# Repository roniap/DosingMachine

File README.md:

# DosingMachine
Automatic dosing sistem for  fertilization

1. PCB EC & PH
2. PROBE STL 3D
3. NEXT TO DO. . . .

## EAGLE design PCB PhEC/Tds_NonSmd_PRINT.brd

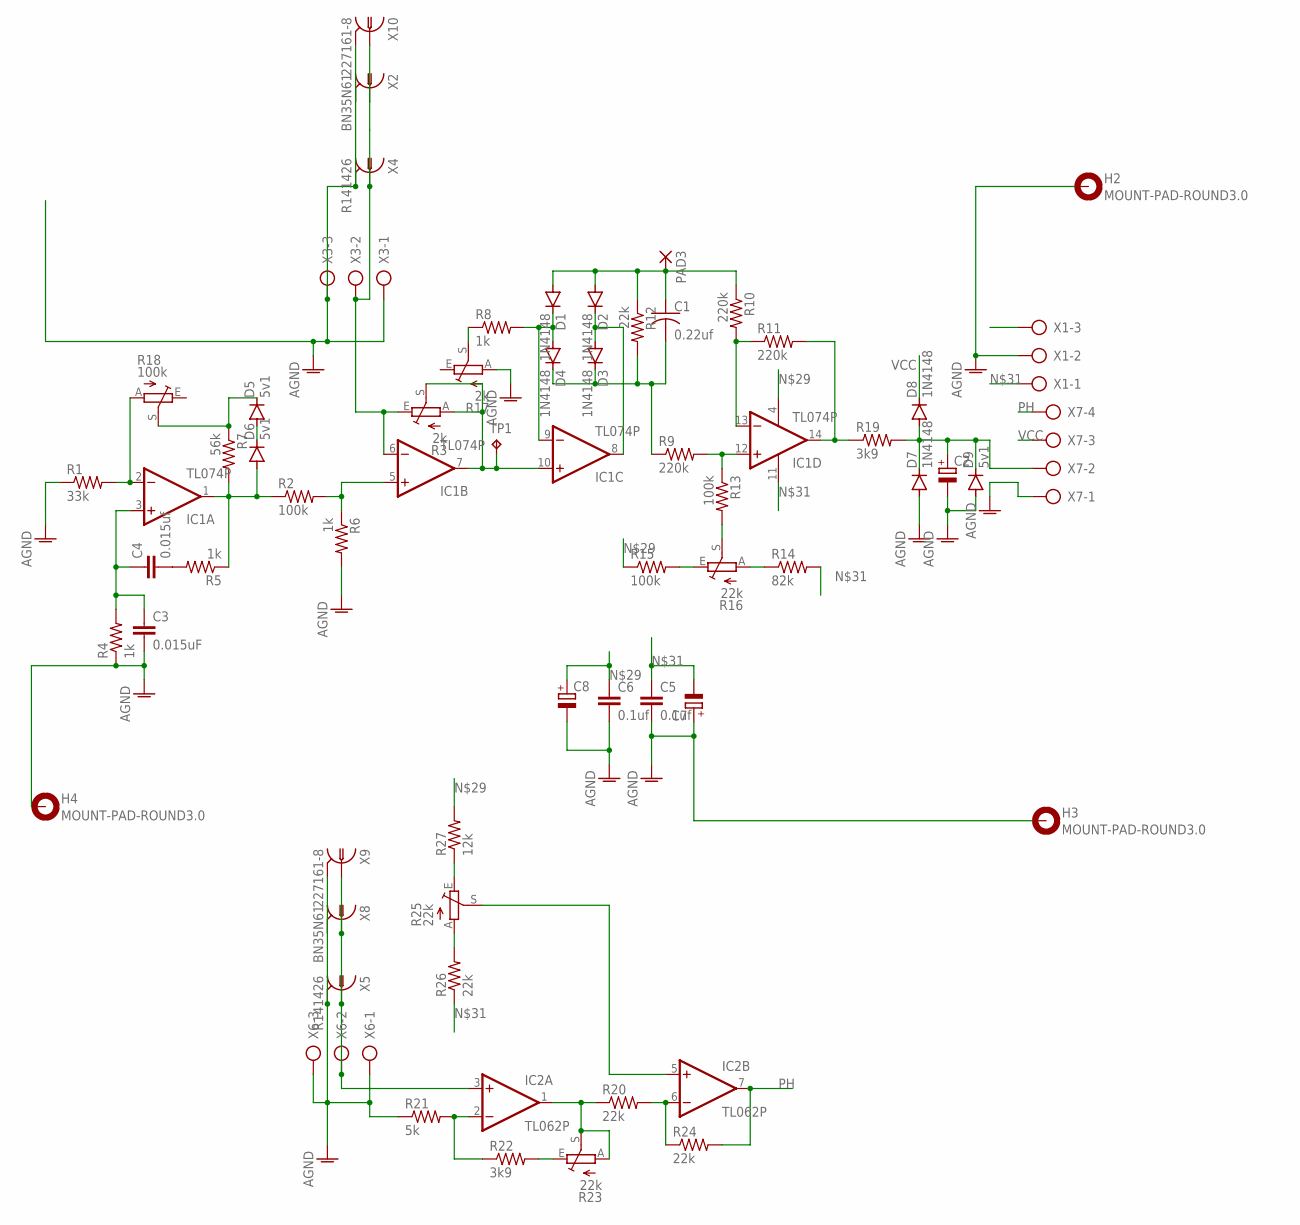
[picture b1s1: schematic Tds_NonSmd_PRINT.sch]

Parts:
C1: 0.22uf; C050-024X044
C2, C7, C8: CPOL-EUE5-8.5; E5-8,5
C3: 0.015uF; C050-024X044
C4: 0.015uf; C050-024X044
C5, C6: 0.1uf; C5B2.5
D1, D2, D3, D4, D7, D8: 1N4148; DO35-7
D5, D6, D9: 5v1; DO35-7
H2, H3, H4: MOUNT-PAD-ROUND3.0; 3,0-PAD
IC1: TL074P; DIL14
IC2: TL062P; DIL08
PAD3: 2,54/1,1
R1: 33k; 0207/7
R2: 100k; 0207/10
R3, R17: 2k; S64W
R4, R5, R6, R8: 1k; 0207/7
R7: 56k; 0207/7
R9, R10, R11: 220k; 0207/7
R12, R20, R24, R26: 22k; 0207/7
R13, R15: 100k; 0207/7
R14: 82k; 0207/7
R16, R23, R25: 22k; S64W
R18: 100k; S64W
R19, R22: 3k9; 0207/7
R21: 5k; 0207/7
R27: 12k; 0207/7
TP1: TPPAD1-13; P1-13
X1, X3, X6: AK500/3
X2, X8: BN35N61; B35N61
X4, X5: R141426
X7: AK500/4
X9, X10: 227161-8; AMP_227161

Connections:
AGND: C2.-, C3.2, C5.2, C6.2, C7.+, C8.-, D7.A, D9.A, H2.B3,0, H3.B3,0, H4.B3,0, R1.1, R4.1, R6.2, R17.A, R21.1, X1.2, X2.2, X2.3 (2), X2.4 (2), X2.5 (2), X3.1, X3.3, X4.2, X4.3 (2), X4.4 (2), X4.5 (2), X5.2, X5.3 (2), X5.4 (2), X5.5 (2), X6.1, X6.3, X7.1, X8.2, X8.3 (2), X8.4 (2), X8.5 (2), X9.2, X10.2
unnamed: IC1.2 (-IN), R1.2, R18.A
unnamed: IC1.6 (-IN), R3.E, X2.1, X3.2, X4.1, X10.1
unnamed: IC1.5 (+IN), R2.2, R6.1
unnamed: D6.A, IC1.1 (OUT), R2.1, R5.1, R7.2
unnamed: C3.1, C4.1, IC1.3 (+IN), R4.2
unnamed: IC2.3 (+IN), X5.1, X6.2, X8.1, X9.1
unnamed: IC1.7 (OUT), IC1.10 (+IN), R3.A, R3.S, TP1.TP
unnamed: C4.2, R5.2
unnamed: IC1.14 (OUT), R11.2, R19.1
unnamed: C1.1, D1.A, D2.A, PAD3.1, R10.1, R12.1
unnamed: D1.C, D4.A, IC1.9 (-IN), R8.2
unnamed: D2.C, D3.A, IC1.8 (OUT)
unnamed: IC1.13 (-IN), R10.2, R11.1
unnamed: IC1.12 (+IN), R9.2, R13.1
unnamed: D5.C, R7.1, R18.S
unnamed: C1.2, D3.C, D4.C, R9.1, R12.2
unnamed: D5.A, D6.C
unnamed: R13.2, R16.S
unnamed: R14.1, R16.A
unnamed: R15.2, R16.E
unnamed: R8.1, R17.S
unnamed: C2.+, D7.C, D8.A, D9.C, R19.2, X7.2
unnamed: R25.E, R27.1
unnamed: IC2.2 (-IN), R21.2, R22.1
unnamed: R25.A, R26.2
unnamed: IC2.1 (OUT), R20.1, R23.A, R23.S
unnamed: R22.2, R23.E
unnamed: IC2.6 (-IN), R20.2, R24.1
unnamed: C6.1, C8.+, IC1.4 (V+), IC2.8 (V+), R15.1, R27.2, X1.3
unnamed: IC2.5 (+IN), R25.S
unnamed: C5.1, C7.-, IC1.11 (V-), IC2.4 (V-), R14.2, R26.1, X1.1
PH: IC2.7 (OUT), R24.2, X7.4
VCC: D8.C, X7.3

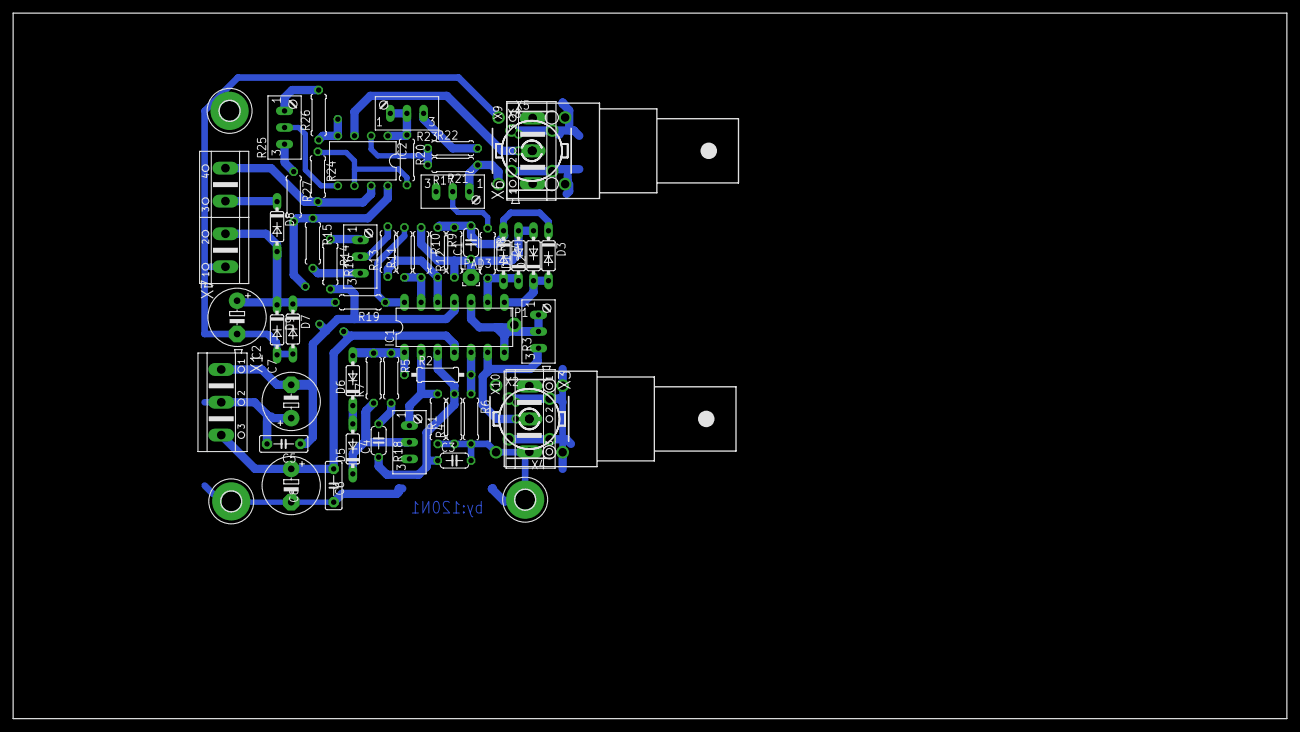
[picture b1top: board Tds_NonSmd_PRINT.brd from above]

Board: 2 copper layers, 194.3 x 107.6 mm, 61 parts (0 on the bottom side), 34 nets.

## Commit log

2019-05-21 PCB DESIGN
2019-05-21 UPDATE pcb NONSMD + UPDATE README
2019-05-21 ADD PCB READY TO PRINT
2019-05-21 3 PRINT PROBE
2019-05-22 UPDATE PCB NON SMD
